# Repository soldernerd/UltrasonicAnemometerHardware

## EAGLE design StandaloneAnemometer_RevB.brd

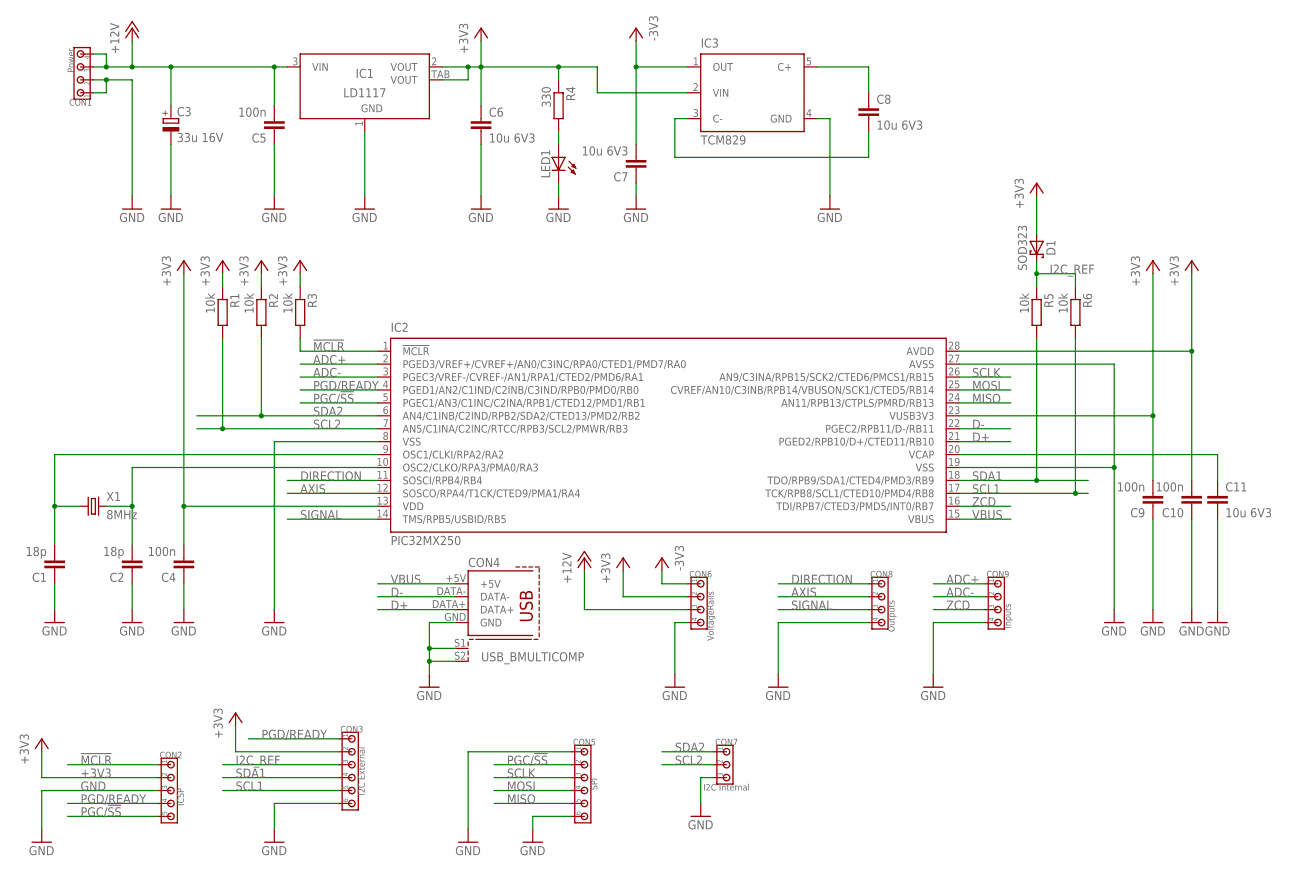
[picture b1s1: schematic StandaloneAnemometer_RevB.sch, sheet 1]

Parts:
C1, C2: 18p; C0805
C3: 33u 16V; SMC_B
C4, C5, C9, C10: 100n; C0805
C6, C7, C8, C11: 10u 6V3; C0805
CON1: Power; 100MIL_4X
CON2: ICSP; 100MIL_5X
CON3: I2C External; 100MIL_6X
CON4: USB_BMULTICOMP; USB_B
CON5: SPI; 100MIL_6X
CON6: VoltageRails; 100MIL_4X
CON7: I2C Internal; 100MIL_3X
CON8: Outputs; 100MIL_4X
CON9: Inputs; 100MIL_4X
D1: SOD323
IC1: LD1117; SOT223
IC2: PIC32MX250; SO28W
IC3: TCM829; SOT-23-5
LED1: LED0805
R1, R2, R3, R5, R6: 10k; R0805
R4: 330; R0805
X1: 8MHz; 5X3.2MM

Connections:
!MCLR!: CON2.1, IC2.1 (!MCLR!), R3.2
+3V3: C4.2, C6.1, C9.2, C10.2, CON2.2, CON3.2, CON6.2, D1.A, IC1.2 (VOUT), IC1.TAB (VOUT), IC2.13 (VDD), IC2.23 (VUSB3V3), IC2.28 (AVDD), IC3.2 (VIN), R1.1, R2.1, R3.1, R4.1; also elsewhere on the board
+12V: C3.+, C5.2, CON1.3, CON1.4, CON6.3, IC1.3 (VIN); also elsewhere on the board
-3V3: C7.2, CON6.1, IC3.1 (OUT); also elsewhere on the board
ADC+: CON9.1, IC2.2 (PGED3/VREF+/CVREF+/AN0/C3INC/RPA0/CTED1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); also elsewhere on the board
ADC-: CON9.2, IC2.3 (PGEC3/VREF-/CVREF-/AN1/RPA1/CTED2/PMD6/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); also elsewhere on the board
AXIS: CON8.2, IC2.12 (SOSCO/RPA4/T1CK/CTED9/PMA1/RA4); also elsewhere on the board
D+: CON4.DATA+, IC2.21 (PGED2/RPB10/D+/CTED11/RB10)
D-: CON4.DATA-, IC2.22 (PGEC2/RPB11/D-/RB11)
DIRECTION: CON8.1, IC2.11 (SOSCI/RPB4/RB4); also elsewhere on the board
GND: C1.1, C2.1, C3.-, C4.1, C5.1, C6.2, C7.1, C9.1, C10.1, C11.2, CON1.1, CON1.2, CON2.3, CON3.6, CON4.GND, CON4.S1, CON4.S2, CON5.1, CON5.6, CON6.4, CON7.3, CON8.4, CON9.4, IC1.1 (GND), IC2.8 (VSS), IC2.19 (VSS), IC2.27 (AVSS), IC3.4 (GND), LED1.C; also elsewhere on the board
I2C_REF: CON3.3, D1.C, R5.1, R6.1
MISO: CON5.5, IC2.24 (AN11/RPB13/CTPLS/PMRD/RB13)
MOSI: CON5.4, IC2.25 (CVREF/AN10/C3INB/RPB14/VBUSON/SCK1/CTED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)
unnamed: LED1.A, R4.2
unnamed: C8.2, IC3.3 (C-)
unnamed: C8.1, IC3.5 (C+)
unnamed: C1.2, IC2.9 (OSC1/CLKI/RPA2/RA2), X1.1
unnamed: C2.2, IC2.10 (OSC2/CLKO/RPA3/PMA0/RA3), X1.2
unnamed: C11.1, IC2.20 (VCAP)
PGC/!SS!: CON2.5, CON5.2, IC2.5 (PGEC1/AN3/C1INC/C2INA/RPB1/CTED12/PMD1/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)
PGD/READY: CON2.4, CON3.1, IC2.4 (PGED1/AN2/C1IND/C2INB/C3IND/RPB0/PMD0/R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)
SCL1: CON3.5, IC2.17 (TCK/RPB8/SCL1/CTED10/PMD4/RB8), R6.2
SCL2: CON7.2, IC2.7 (AN5/C1INA/C2INC/RTCC/RPB3/SCL2/PMWR/RB3), R1.2; also elsewhere on the board
SCLK: CON5.3, IC2.26 (AN9/C3INA/RPB15/SCK2/CTED6/PMCS1/RB15)
SDA1: CON3.4, IC2.18 (TDO/RPB9/SDA1/CTED4/PMD3/RB9), R5.2
SDA2: CON7.1, IC2.6 (AN4/C1INB/C2IND/RPB2/SDA2/CTED13/PMD2/R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), R2.2; also elsewhere on the board
SIGNAL: CON8.3, IC2.14 (TMS/RPB5/USBID/RB5); also elsewhere on the board
VBUS: CON4.+5V, IC2.15 (VBUS)
ZCD: CON9.3, IC2.16 (TDI/RPB7/CTED3/PMD5/INT0/RB7); also elsewhere on the board

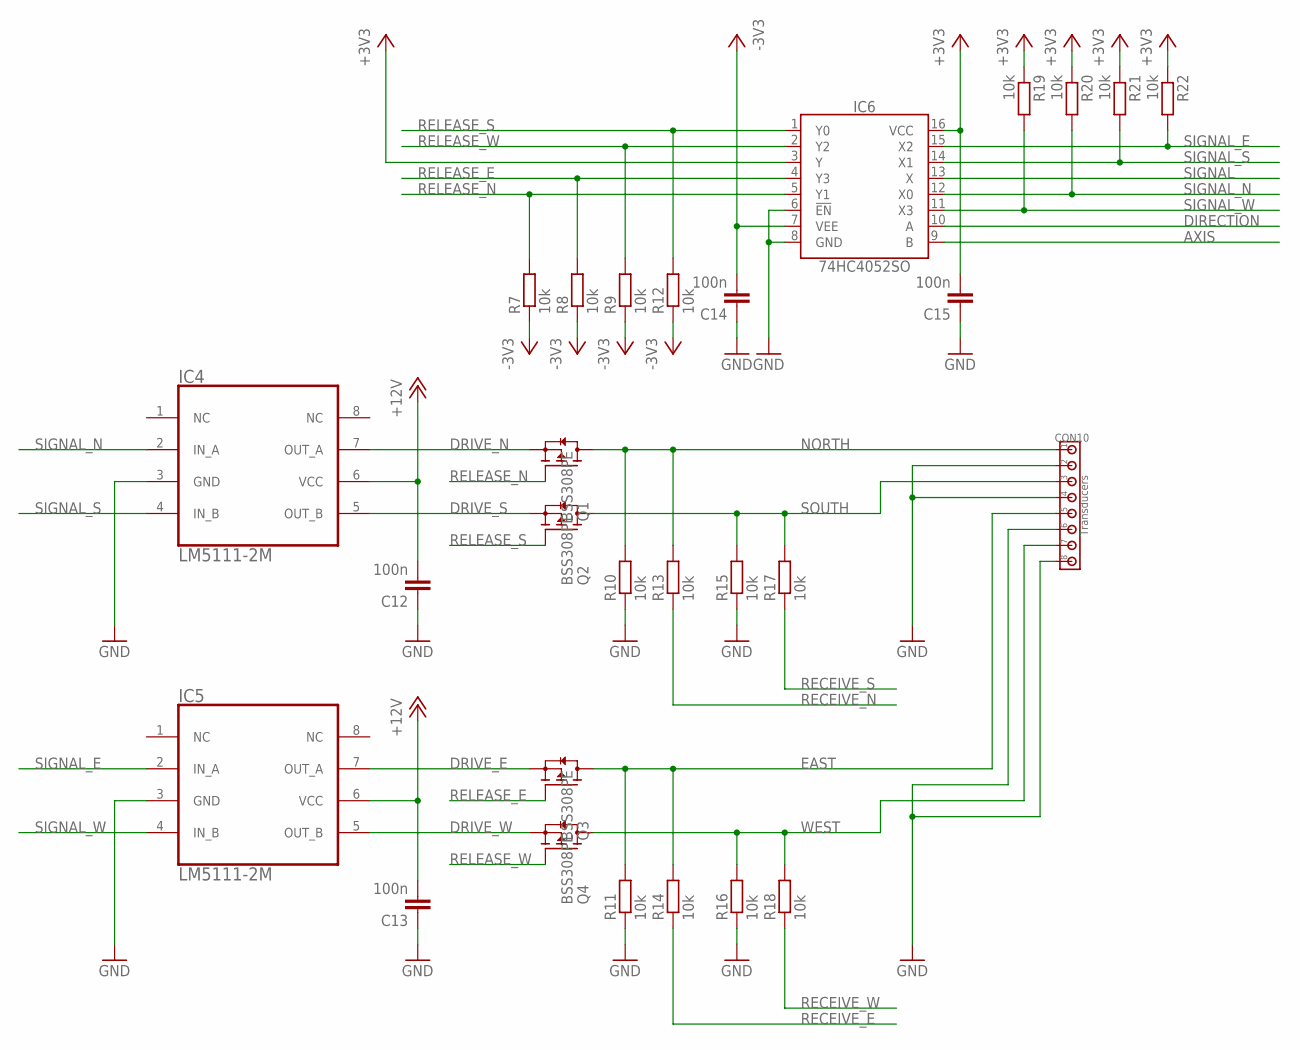
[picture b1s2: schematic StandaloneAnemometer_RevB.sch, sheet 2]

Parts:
C12, C13, C14, C15: 100n; C0805
CON10: Transducers; 100MIL_8X
IC4, IC5: LM5111-2M; SOIC8
IC6: 74HC4052SO; SO16
Q1, Q2, Q3, Q4: BSS308PE; SOT23
R7, R8, R9, R10, R11, R12, R13, R14, R15, R16, R17, R18, R19, R20, R21, R22: 10k; R0805

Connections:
+3V3: C15.2, IC6.3 (Y), IC6.16 (VCC), R19.1, R20.1, R21.1, R22.1; also elsewhere on the board
+12V: C12.2, C13.2, IC4.6 (VCC), IC5.6 (VCC); also elsewhere on the board
-3V3: C14.2, IC6.7 (VEE), R7.1, R8.1, R9.1, R12.1; also elsewhere on the board
AXIS: IC6.9 (B); also elsewhere on the board
DIRECTION: IC6.10 (A); also elsewhere on the board
DRIVE_E: IC5.7 (OUT_A), Q3.2 (S)
DRIVE_N: IC4.7 (OUT_A), Q1.2 (S)
DRIVE_S: IC4.5 (OUT_B), Q2.2 (S)
DRIVE_W: IC5.5 (OUT_B), Q4.2 (S)
EAST: CON10.5, Q3.3 (D), R11.2, R14.2
GND: C12.1, C13.1, C14.1, C15.1, CON10.2, CON10.4, CON10.6, CON10.8, IC4.3 (GND), IC5.3 (GND), IC6.6 (!EN!), IC6.8 (GND), R10.1, R11.1, R15.1, R16.1; also elsewhere on the board
NORTH: CON10.1, Q1.3 (D), R10.2, R13.2
RECEIVE_E: R14.1; also elsewhere on the board
RECEIVE_N: R13.1; also elsewhere on the board
RECEIVE_S: R17.1; also elsewhere on the board
RECEIVE_W: R18.1; also elsewhere on the board
RELEASE_E: IC6.4 (Y3), Q3.1 (G), R8.2
RELEASE_N: IC6.5 (Y1), Q1.1 (G), R7.2
RELEASE_S: IC6.1 (Y0), Q2.1 (G), R12.2
RELEASE_W: IC6.2 (Y2), Q4.1 (G), R9.2
SIGNAL: IC6.13 (X); also elsewhere on the board
SIGNAL_E: IC5.2 (IN_A), IC6.15 (X2), R22.2
SIGNAL_N: IC4.2 (IN_A), IC6.12 (X0), R20.2
SIGNAL_S: IC4.4 (IN_B), IC6.14 (X1), R21.2
SIGNAL_W: IC5.4 (IN_B), IC6.11 (X3), R19.2
SOUTH: CON10.3, Q2.3 (D), R15.2, R17.2
WEST: CON10.7, Q4.3 (D), R16.2, R18.2

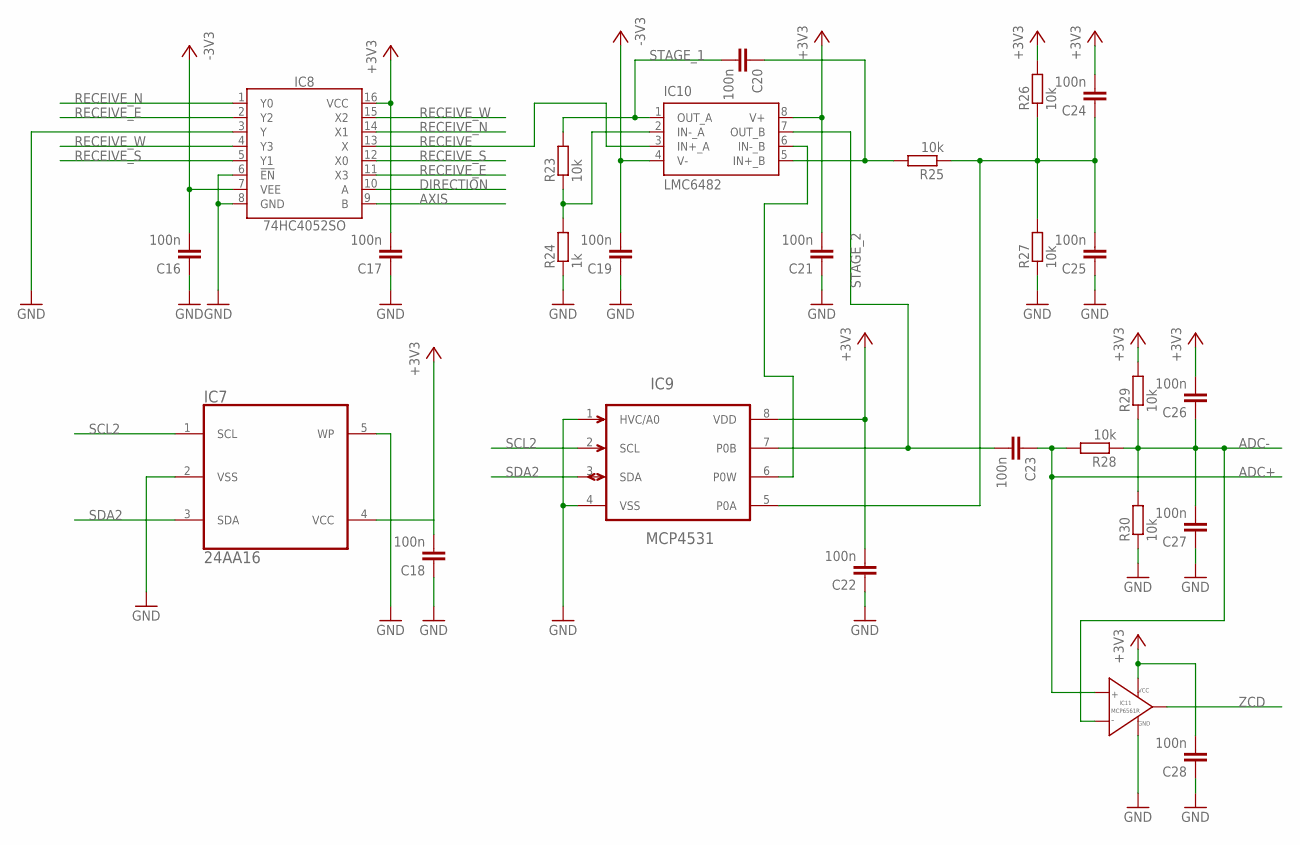
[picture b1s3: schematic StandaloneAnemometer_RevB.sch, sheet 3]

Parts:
C16, C17, C18, C19, C20, C21, C22, C23, C24, C25, C26, C27, C28: 100n; C0805
IC7: 24AA16; SOT-23-5
IC8: 74HC4052SO; SO16
IC9: MCP4531; MSOP
IC10: LMC6482; SOIC8
IC11: MCP6561R; SOT-23-5
R23, R25, R26, R27, R28, R29, R30: 10k; R0805
R24: 1k; R0805

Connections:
+3V3: C17.2, C18.2, C21.2, C22.2, C24.2, C26.2, C28.2, IC7.4 (VCC), IC8.16 (VCC), IC9.8 (VDD), IC10.8 (V+), IC11.2 (VCC), R26.2, R29.2; also elsewhere on the board
-3V3: C16.2, C19.2, IC8.7 (VEE), IC10.4 (V-); also elsewhere on the board
ADC+: C23.1, IC11.3 (VIN+), R28.2; also elsewhere on the board
ADC-: C26.1, C27.2, IC11.4 (VIN-), R28.1, R29.1, R30.2; also elsewhere on the board
AXIS: IC8.9 (B); also elsewhere on the board
DIRECTION: IC8.10 (A); also elsewhere on the board
FB1: IC10.2 (IN-_A), R23.1, R24.2
FB2: IC9.6 (P0W), IC10.6 (IN-_B)
GND: C16.1, C17.1, C18.1, C19.1, C21.1, C22.1, C25.1, C27.1, C28.1, IC7.2 (VSS), IC7.5 (WP), IC8.3 (Y), IC8.6 (!EN!), IC8.8 (GND), IC9.1 (HVC/A0), IC9.4 (VSS), IC11.5 (GND), R24.1, R27.1, R30.1; also elsewhere on the board
unnamed: C24.1, C25.2, IC9.5 (P0A), R25.1, R26.1, R27.2
RECEIVE: IC8.13 (X), IC10.3 (IN+_A)
RECEIVE_E: IC8.2 (Y2), IC8.11 (X3); also elsewhere on the board
RECEIVE_N: IC8.1 (Y0), IC8.14 (X1); also elsewhere on the board
RECEIVE_S: IC8.5 (Y1), IC8.12 (X0); also elsewhere on the board
RECEIVE_W: IC8.4 (Y3), IC8.15 (X2); also elsewhere on the board
SCL2: IC7.1 (SCL), IC9.2 (SCL); also elsewhere on the board
SDA2: IC7.3 (SDA), IC9.3 (SDA); also elsewhere on the board
STAGE2_IN: C20.1, IC10.5 (IN+_B), R25.2
STAGE_1: C20.2, IC10.1 (OUT_A), R23.2
STAGE_2: C23.2, IC9.7 (P0B), IC10.7 (OUT_B)
ZCD: IC11.1 (VOUT); also elsewhere on the board

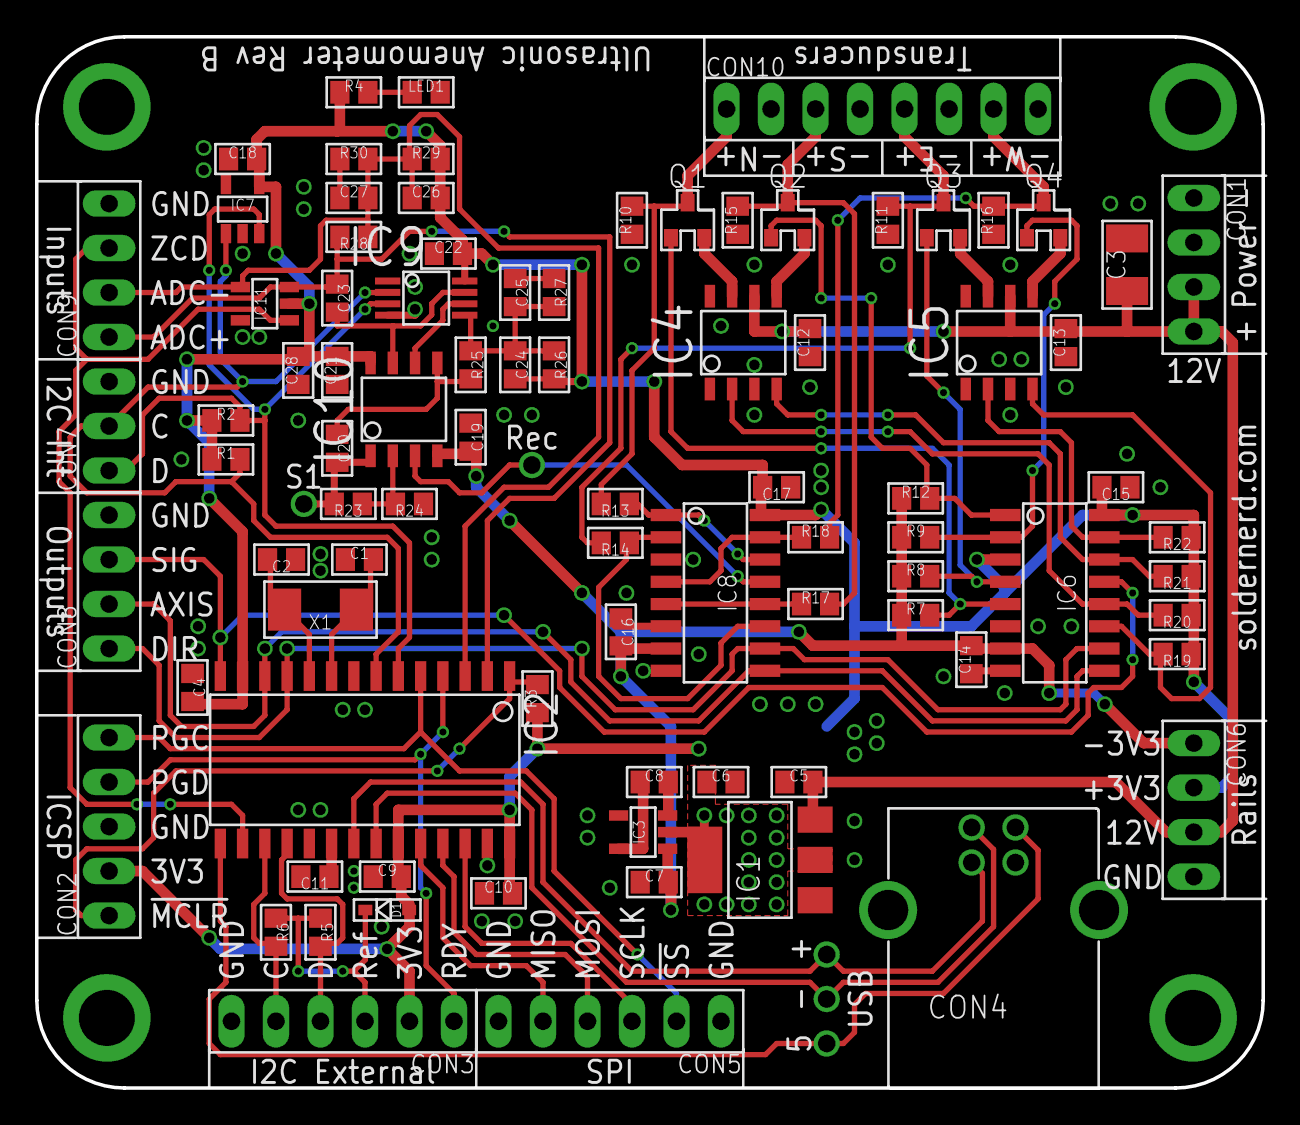
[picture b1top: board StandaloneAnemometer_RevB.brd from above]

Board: 2 copper layers, 70.0 x 60.0 mm, 86 parts (0 on the bottom side), 57 nets.

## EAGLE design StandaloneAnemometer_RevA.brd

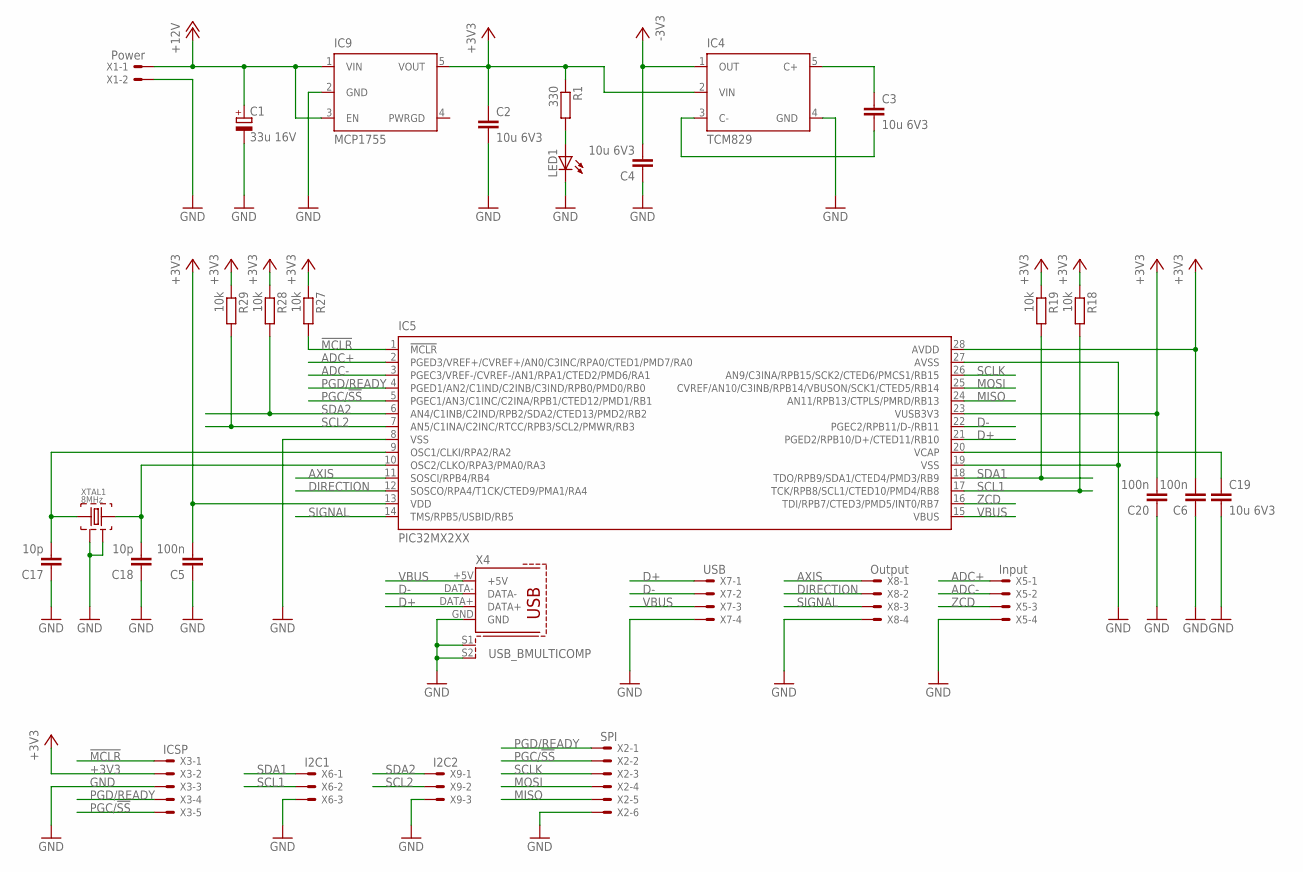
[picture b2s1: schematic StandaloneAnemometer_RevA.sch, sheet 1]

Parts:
C1: 33u 16V; SMC_B
C2, C3, C4, C19: 10u 6V3; C0805
C5, C6, C20: 100n; C0805
C17, C18: 10p; C0805
IC4: TCM829; SOT-23-5
IC5: PIC32MX2XX; SO28W
IC9: MCP1755; SOT-23-5
LED1: LED0805
R1: 330; R0805
R18, R19, R27, R28, R29: 10k; R0805
X1: Power; 22-23-2021
X2: SPI; 22-23-2061
X3: ICSP; 22-23-2051
X4: USB_BMULTICOMP; USB_B
X5: Input; 22-23-2041
X6: I2C1; 22-23-2031
X7: USB; 22-23-2041
X8: Output; 22-23-2041
X9: I2C2; 22-23-2031
XTAL1: 8MHz; 5X3.2MM

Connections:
!MCLR!: IC5.1 (!MCLR!), R27.2, X3.1
+3V3: C2.1, C5.2, C6.2, C20.2, IC4.2 (VIN), IC5.13 (VDD), IC5.23 (VUSB3V3), IC5.28 (AVDD), IC9.5 (VOUT), R1.1, R18.1, R19.1, R27.1, R28.1, R29.1, X3.2; also elsewhere on the board
+12V: C1.+, IC9.1 (VIN), IC9.3 (EN), X1.1; also elsewhere on the board
-3V3: C4.2, IC4.1 (OUT); also elsewhere on the board
ADC+: IC5.2 (PGED3/VREF+/CVREF+/AN0/C3INC/RPA0/CTED1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), X5.1; also elsewhere on the board
ADC-: IC5.3 (PGEC3/VREF-/CVREF-/AN1/RPA1/CTED2/PMD6/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), X5.2; also elsewhere on the board
AXIS: IC5.11 (SOSCI/RPB4/RB4), X8.1; also elsewhere on the board
D+: IC5.21 (PGED2/RPB10/D+/CTED11/RB10), X4.DATA+, X7.1
D-: IC5.22 (PGEC2/RPB11/D-/RB11), X4.DATA-, X7.2
DIRECTION: IC5.12 (SOSCO/RPA4/T1CK/CTED9/PMA1/RA4), X8.2; also elsewhere on the board
GND: C1.-, C2.2, C4.1, C5.1, C6.1, C17.1, C18.1, C19.2, C20.1, IC4.4 (GND), IC5.8 (VSS), IC5.19 (VSS), IC5.27 (AVSS), IC9.2 (GND), LED1.C, X1.2, X2.6, X3.3, X4.GND, X4.S1, X4.S2, X5.4, X6.3, X7.4, X8.4, X9.3, XTAL1.2, XTAL1.4; also elsewhere on the board
MISO: IC5.24 (AN11/RPB13/CTPLS/PMRD/RB13), X2.5
MOSI: IC5.25 (CVREF/AN10/C3INB/RPB14/VBUSON/SCK1/CTED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), X2.4
unnamed: LED1.A, R1.2
unnamed: C3.2, IC4.3 (C-)
unnamed: C3.1, IC4.5 (C+)
unnamed: C17.2, IC5.9 (OSC1/CLKI/RPA2/RA2), XTAL1.1
unnamed: C18.2, IC5.10 (OSC2/CLKO/RPA3/PMA0/RA3), XTAL1.3
unnamed: C19.1, IC5.20 (VCAP)
PGC/!SS!: IC5.5 (PGEC1/AN3/C1INC/C2INA/RPB1/CTED12/PMD1/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), X2.2, X3.5
PGD/READY: IC5.4 (PGED1/AN2/C1IND/C2INB/C3IND/RPB0/PMD0/R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), X2.1, X3.4
SCL1: IC5.17 (TCK/RPB8/SCL1/CTED10/PMD4/RB8), R18.2, X6.2
SCL2: IC5.7 (AN5/C1INA/C2INC/RTCC/RPB3/SCL2/PMWR/RB3), R29.2, X9.2; also elsewhere on the board
SCLK: IC5.26 (AN9/C3INA/RPB15/SCK2/CTED6/PMCS1/RB15), X2.3
SDA1: IC5.18 (TDO/RPB9/SDA1/CTED4/PMD3/RB9), R19.2, X6.1
SDA2: IC5.6 (AN4/C1INB/C2IND/RPB2/SDA2/CTED13/PMD2/R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), R28.2, X9.1; also elsewhere on the board
SIGNAL: IC5.14 (TMS/RPB5/USBID/RB5), X8.3; also elsewhere on the board
VBUS: IC5.15 (VBUS), X4.+5V, X7.3
ZCD: IC5.16 (TDI/RPB7/CTED3/PMD5/INT0/RB7), X5.3; also elsewhere on the board

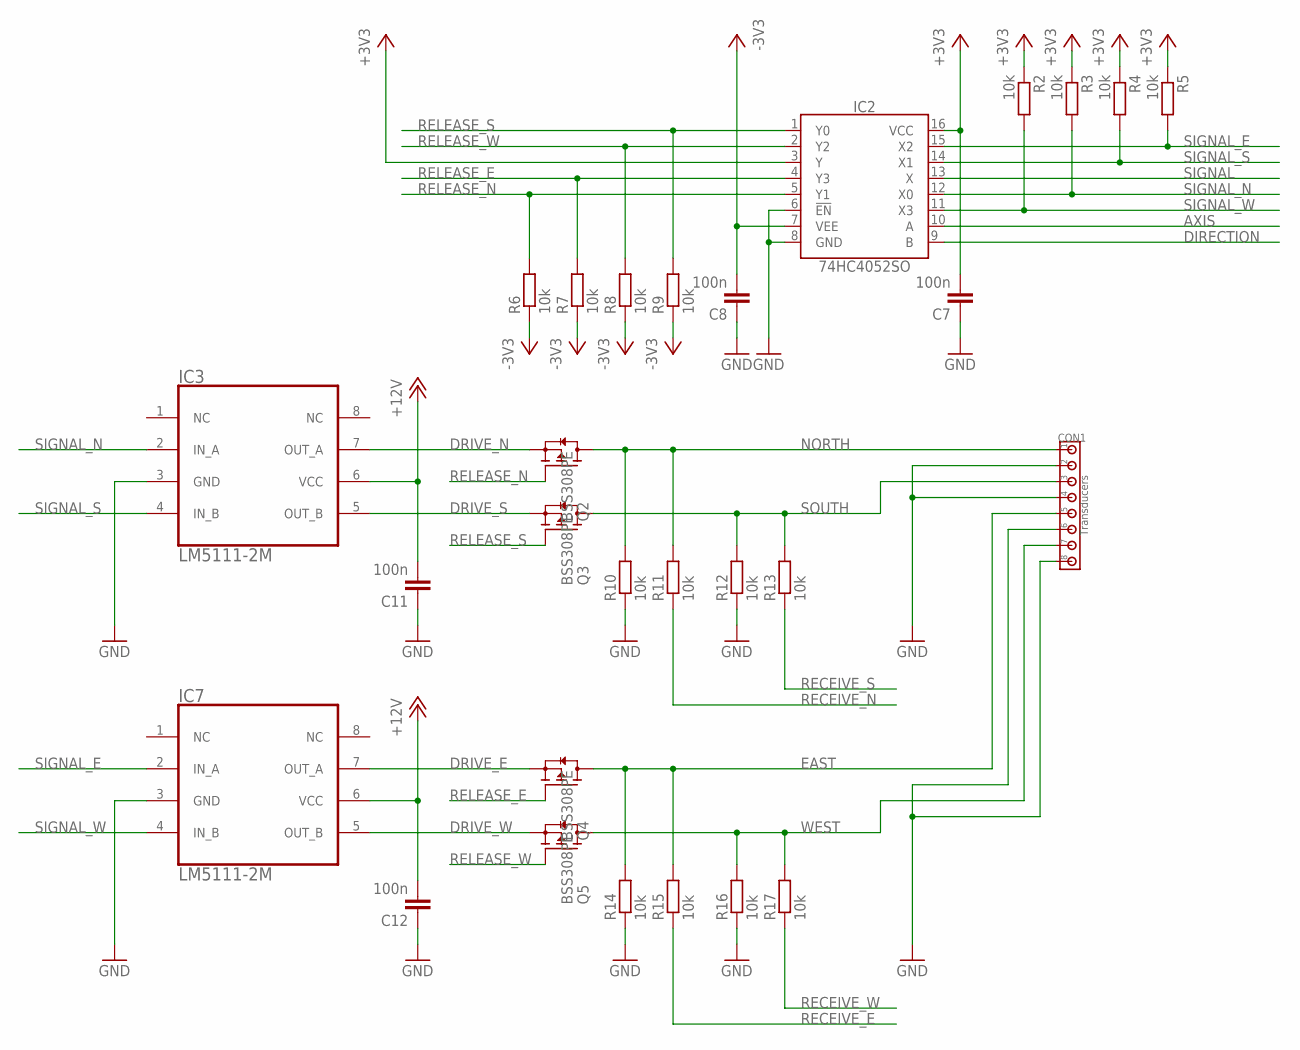
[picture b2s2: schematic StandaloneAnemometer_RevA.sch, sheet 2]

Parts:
C7, C8, C11, C12: 100n; C0805
CON1: Transducers; 3.5MM_8X
IC2: 74HC4052SO; SO16
IC3, IC7: LM5111-2M; SOIC8
Q2, Q3, Q4, Q5: BSS308PE; SOT23
R2, R3, R4, R5, R6, R7, R8, R9, R10, R11, R12, R13, R14, R15, R16, R17: 10k; R0805

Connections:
+3V3: C7.2, IC2.3 (Y), IC2.16 (VCC), R2.1, R3.1, R4.1, R5.1; also elsewhere on the board
+12V: C11.2, C12.2, IC3.6 (VCC), IC7.6 (VCC); also elsewhere on the board
-3V3: C8.2, IC2.7 (VEE), R6.1, R7.1, R8.1, R9.1; also elsewhere on the board
AXIS: IC2.10 (A); also elsewhere on the board
DIRECTION: IC2.9 (B); also elsewhere on the board
DRIVE_E: IC7.7 (OUT_A), Q4.2 (S)
DRIVE_N: IC3.7 (OUT_A), Q2.2 (S)
DRIVE_S: IC3.5 (OUT_B), Q3.2 (S)
DRIVE_W: IC7.5 (OUT_B), Q5.2 (S)
EAST: CON1.5, Q4.3 (D), R14.2, R15.2
GND: C7.1, C8.1, C11.1, C12.1, CON1.2, CON1.4, CON1.6, CON1.8, IC2.6 (!EN!), IC2.8 (GND), IC3.3 (GND), IC7.3 (GND), R10.1, R12.1, R14.1, R16.1; also elsewhere on the board
NORTH: CON1.1, Q2.3 (D), R10.2, R11.2
RECEIVE_E: R15.1; also elsewhere on the board
RECEIVE_N: R11.1; also elsewhere on the board
RECEIVE_S: R13.1; also elsewhere on the board
RECEIVE_W: R17.1; also elsewhere on the board
RELEASE_E: IC2.4 (Y3), Q4.1 (G), R7.2
RELEASE_N: IC2.5 (Y1), Q2.1 (G), R6.2
RELEASE_S: IC2.1 (Y0), Q3.1 (G), R9.2
RELEASE_W: IC2.2 (Y2), Q5.1 (G), R8.2
SIGNAL: IC2.13 (X); also elsewhere on the board
SIGNAL_E: IC2.15 (X2), IC7.2 (IN_A), R5.2
SIGNAL_N: IC2.12 (X0), IC3.2 (IN_A), R3.2
SIGNAL_S: IC2.14 (X1), IC3.4 (IN_B), R4.2
SIGNAL_W: IC2.11 (X3), IC7.4 (IN_B), R2.2
SOUTH: CON1.3, Q3.3 (D), R12.2, R13.2
WEST: CON1.7, Q5.3 (D), R16.2, R17.2

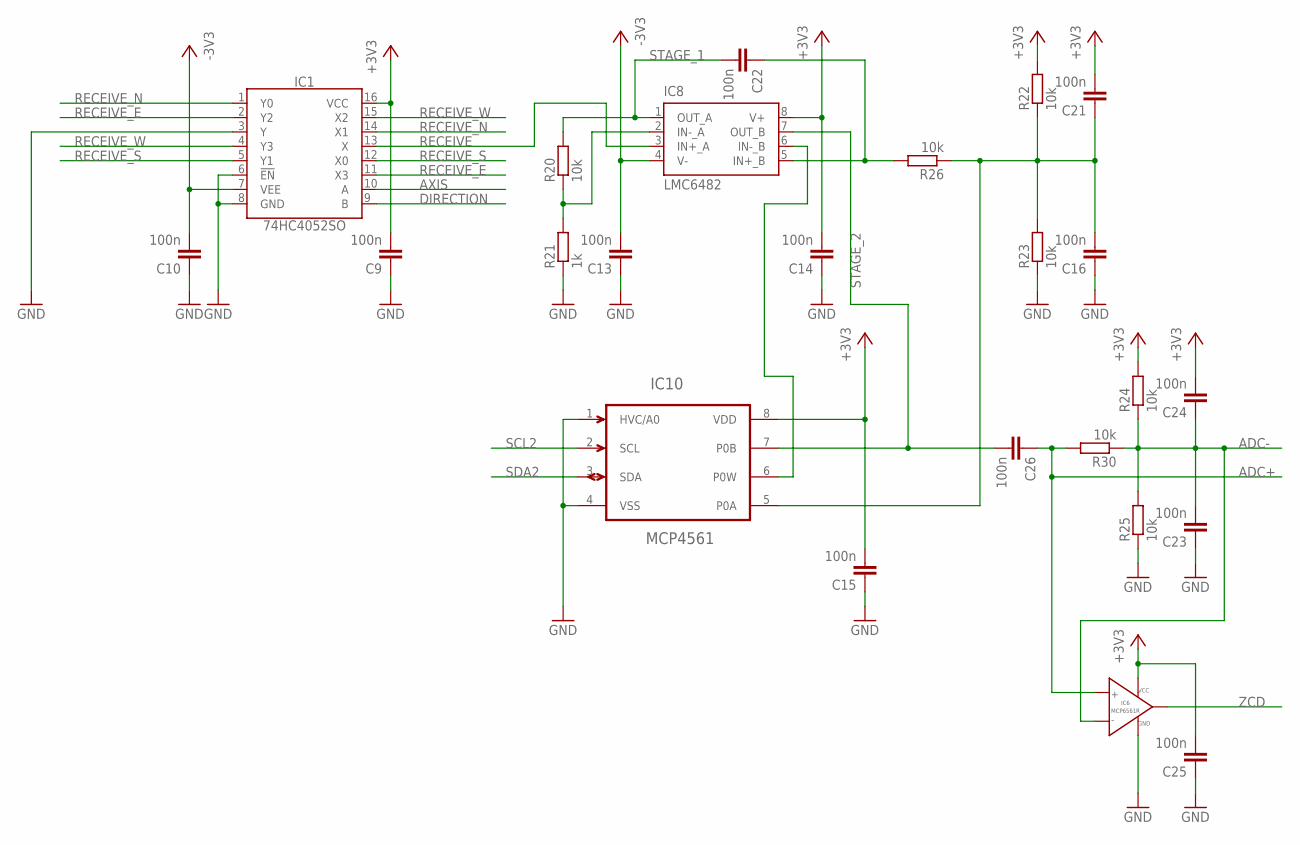
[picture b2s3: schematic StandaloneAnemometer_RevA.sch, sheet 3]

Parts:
C9, C10, C13, C14, C15, C16, C21, C22, C23, C24, C25, C26: 100n; C0805
IC1: 74HC4052SO; SO16
IC6: MCP6561R; SOT-23-5
IC8: LMC6482; SOIC8
IC10: MCP4561; MSOP
R20, R22, R23, R24, R25, R26, R30: 10k; R0805
R21: 1k; R0805

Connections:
+3V3: C9.2, C14.2, C15.2, C21.2, C24.2, C25.2, IC1.16 (VCC), IC6.2 (VCC), IC8.8 (V+), IC10.8 (VDD), R22.2, R24.2; also elsewhere on the board
-3V3: C10.2, C13.2, IC1.7 (VEE), IC8.4 (V-); also elsewhere on the board
ADC+: C26.1, IC6.3 (VIN+), R30.2; also elsewhere on the board
ADC-: C23.2, C24.1, IC6.4 (VIN-), R24.1, R25.2, R30.1; also elsewhere on the board
AXIS: IC1.10 (A); also elsewhere on the board
DIRECTION: IC1.9 (B); also elsewhere on the board
FB1: IC8.2 (IN-_A), R20.1, R21.2
FB2: IC8.6 (IN-_B), IC10.6 (P0W)
GND: C9.1, C10.1, C13.1, C14.1, C15.1, C16.1, C23.1, C25.1, IC1.3 (Y), IC1.6 (!EN!), IC1.8 (GND), IC6.5 (GND), IC10.1 (HVC/A0), IC10.4 (VSS), R21.1, R23.1, R25.1; also elsewhere on the board
unnamed: C16.2, C21.1, IC10.5 (P0A), R22.1, R23.2, R26.1
RECEIVE: IC1.13 (X), IC8.3 (IN+_A)
RECEIVE_E: IC1.2 (Y2), IC1.11 (X3); also elsewhere on the board
RECEIVE_N: IC1.1 (Y0), IC1.14 (X1); also elsewhere on the board
RECEIVE_S: IC1.5 (Y1), IC1.12 (X0); also elsewhere on the board
RECEIVE_W: IC1.4 (Y3), IC1.15 (X2); also elsewhere on the board
SCL2: IC10.2 (SCL); also elsewhere on the board
SDA2: IC10.3 (SDA); also elsewhere on the board
STAGE2_IN: C22.1, IC8.5 (IN+_B), R26.2
STAGE_1: C22.2, IC8.1 (OUT_A), R20.2
STAGE_2: C26.2, IC8.7 (OUT_B), IC10.7 (P0B)
ZCD: IC6.1 (VOUT); also elsewhere on the board

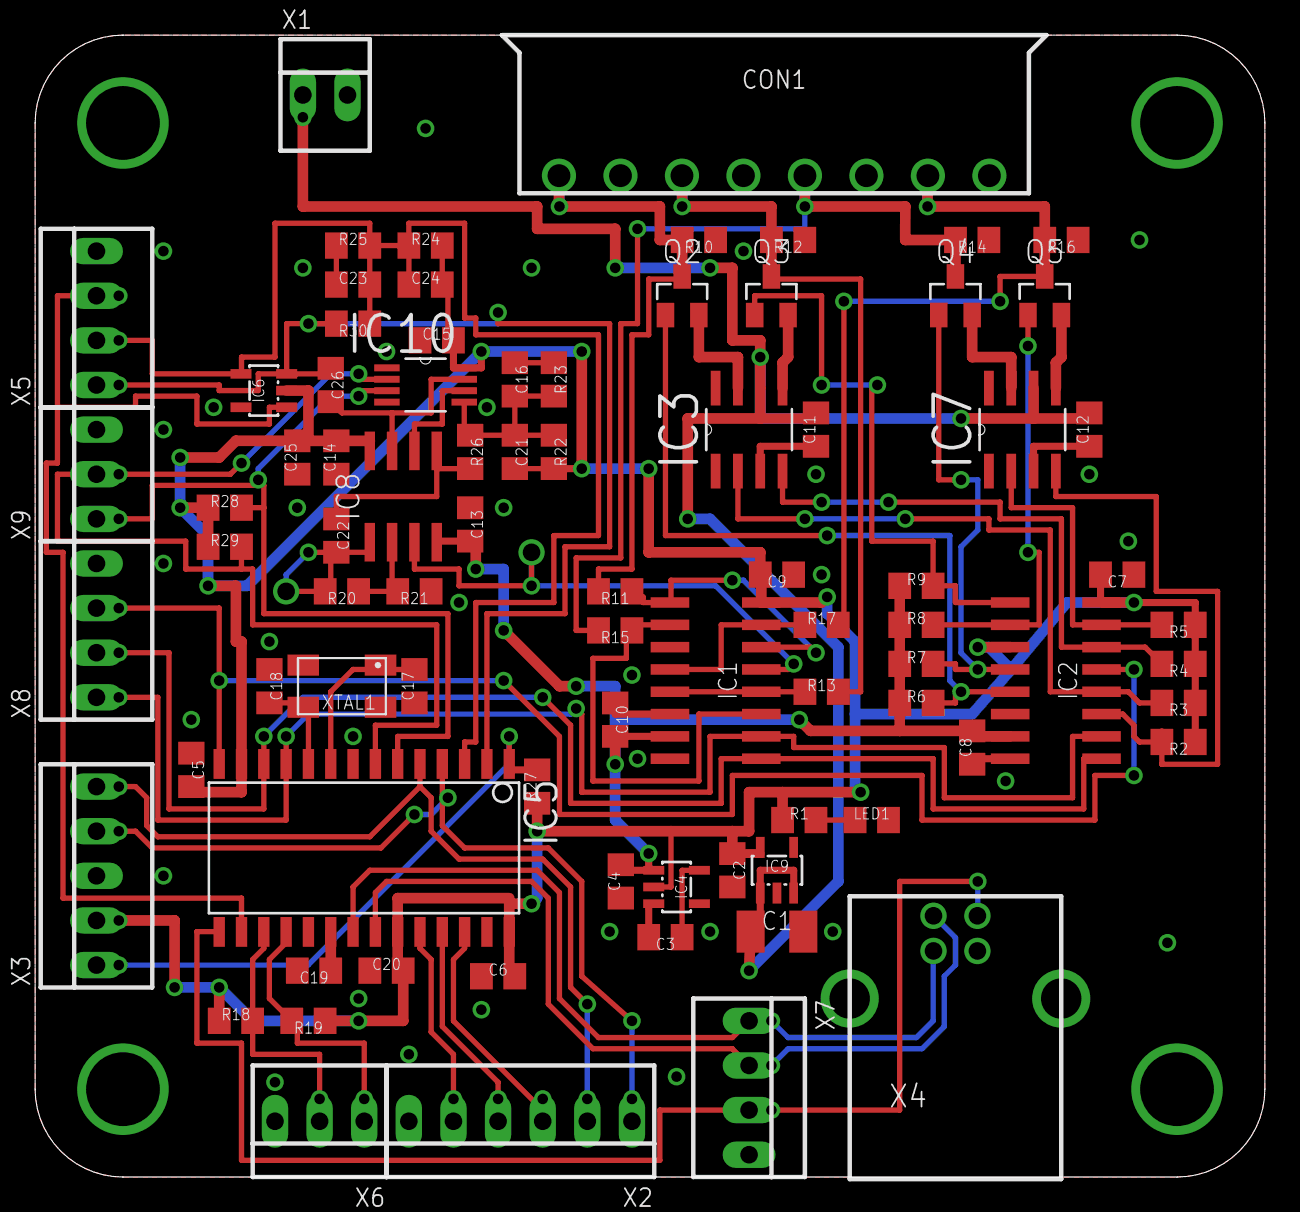
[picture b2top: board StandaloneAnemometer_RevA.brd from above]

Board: 2 copper layers, 70.0 x 65.0 mm, 82 parts (0 on the bottom side), 56 nets.

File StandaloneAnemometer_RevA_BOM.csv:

"Qty";"Value";"Device";"Package";"Parts";"Description";"MF";"MPN";"OC_FARNELL";"OC_NEWARK";
"1";"";"LED0805";"LED0805";"LED1";"LED";"";"";"";"";
"19";"100n";"CC0805";"C0805";"C5, C6, C7, C8, C9, C10, C11, C12, C13, C14, C15, C16, C20, C21, C22, C23, C24, C25, C26";"Capacitor";"";"";"";"";
"28";"10k";"RESISTORR0805";"R0805";"R2, R3, R4, R5, R6, R7, R8, R9, R10, R11, R12, R13, R14, R15, R16, R17, R18, R19, R20, R22, R23, R24, R25, R26, R27, R28, R29, R30";"RESISTOR, European symbol";"";"";"";"";
"2";"10p";"CC0805";"C0805";"C17, C18";"Capacitor";"";"";"";"";
"4";"10u 6V3";"CC0805";"C0805";"C2, C3, C4, C19";"Capacitor";"";"";"";"";
"1";"1k";"RESISTORR0805";"R0805";"R21";"RESISTOR, European symbol";"";"";"";"";
"1";"330";"RESISTORR0805";"R0805";"R1";"RESISTOR, European symbol";"";"";"";"";
"1";"33u 16V";"C_POLARIZEDSMC_B";"SMC_B";"C1";"";"";"";"";"";
"2";"74HC4052SO";"74HC4052SO";"SO16";"IC1, IC2";"";"";"";"";"";
"1";"8MHz";"CRYSTAL_SHIELDED";"5X3.2MM";"XTAL1";"Shielded Crystal";"";"";"";"";
"4";"BSS308PE";"P-FET";"SOT23";"Q2, Q3, Q4, Q5";"";"";"";"";"";
"1";"I2C1";"22-23-2031";"22-23-2031";"X6";".100" (2.54mm) Center Header - 3 Pin";"MOLEX";"22-23-2031";"1462950";"30C0862";
"1";"I2C2";"22-23-2031";"22-23-2031";"X9";".100" (2.54mm) Center Header - 3 Pin";"MOLEX";"22-23-2031";"1462950";"30C0862";
"1";"ICSP";"22-23-2051";"22-23-2051";"X3";".100" (2.54mm) Center Header - 5 Pin";"MOLEX";"22-23-2051";"1462952";"38C9178";
"1";"Input";"22-23-20411MM";"22-23-2041";"X5";".100" (2.54mm) Center Header - 4 Pin";"";"";"";"";
"2";"LM5111-2M";"LM5111";"SOIC8";"IC3, IC7";"Dual 5A Compound Gate Driver";"";"";"";"";
"1";"LMC6482";"LMC6482";"SOIC8";"IC8";"CMOS Dual Rail-to-Rail Input and Output Operational Amplifier";"";"";"";"";
"1";"MCP1755";"MCP1755";"SOT-23-5";"IC9";"";"";"";"";"";
"1";"MCP4561";"MCP4561MSOP";"MSOP";"IC10";"Digital POT";"";"";"";"";
"1";"MCP6561R";"MCP6561R";"SOT-23-5";"IC6";"1.8V Low-Power Push-Pull Output Comparator";"";"";"";"";
"1";"Output";"22-23-20411MM";"22-23-2041";"X8";".100" (2.54mm) Center Header - 4 Pin";"";"";"";"";
"1";"PIC32MX2XX";"PIC32MX2XX";"SO28W";"IC5";"";"";"";"";"";
"1";"Power";"22-23-2021100MIL";"22-23-2021";"X1";".100" (2.54mm) Center Header - 2 Pin";"MOLEX";"22-23-2021";"1462926";"25C3832";
"1";"SPI";"22-23-2061";"22-23-2061";"X2";".100" (2.54mm) Center Header - 6 Pin";"MOLEX";"22-23-2061";"1462922";"27C1933";
"1";"TCM829";"TCM829";"SOT-23-5";"IC4";"";"";"";"";"";
"1";"Transducers";"CON_8X3.5MM";"3.5MM_8X";"CON1";"8-pin header";"";"";"";"";
"1";"USB";"22-23-20411MM";"22-23-2041";"X7";".100" (2.54mm) Center Header - 4 Pin";"";"";"";"";
"1";"USB_BMULTICOMP";"USB_BMULTICOMP";"USB_B";"X4";"Type B USB connector";"";"";"";"";
